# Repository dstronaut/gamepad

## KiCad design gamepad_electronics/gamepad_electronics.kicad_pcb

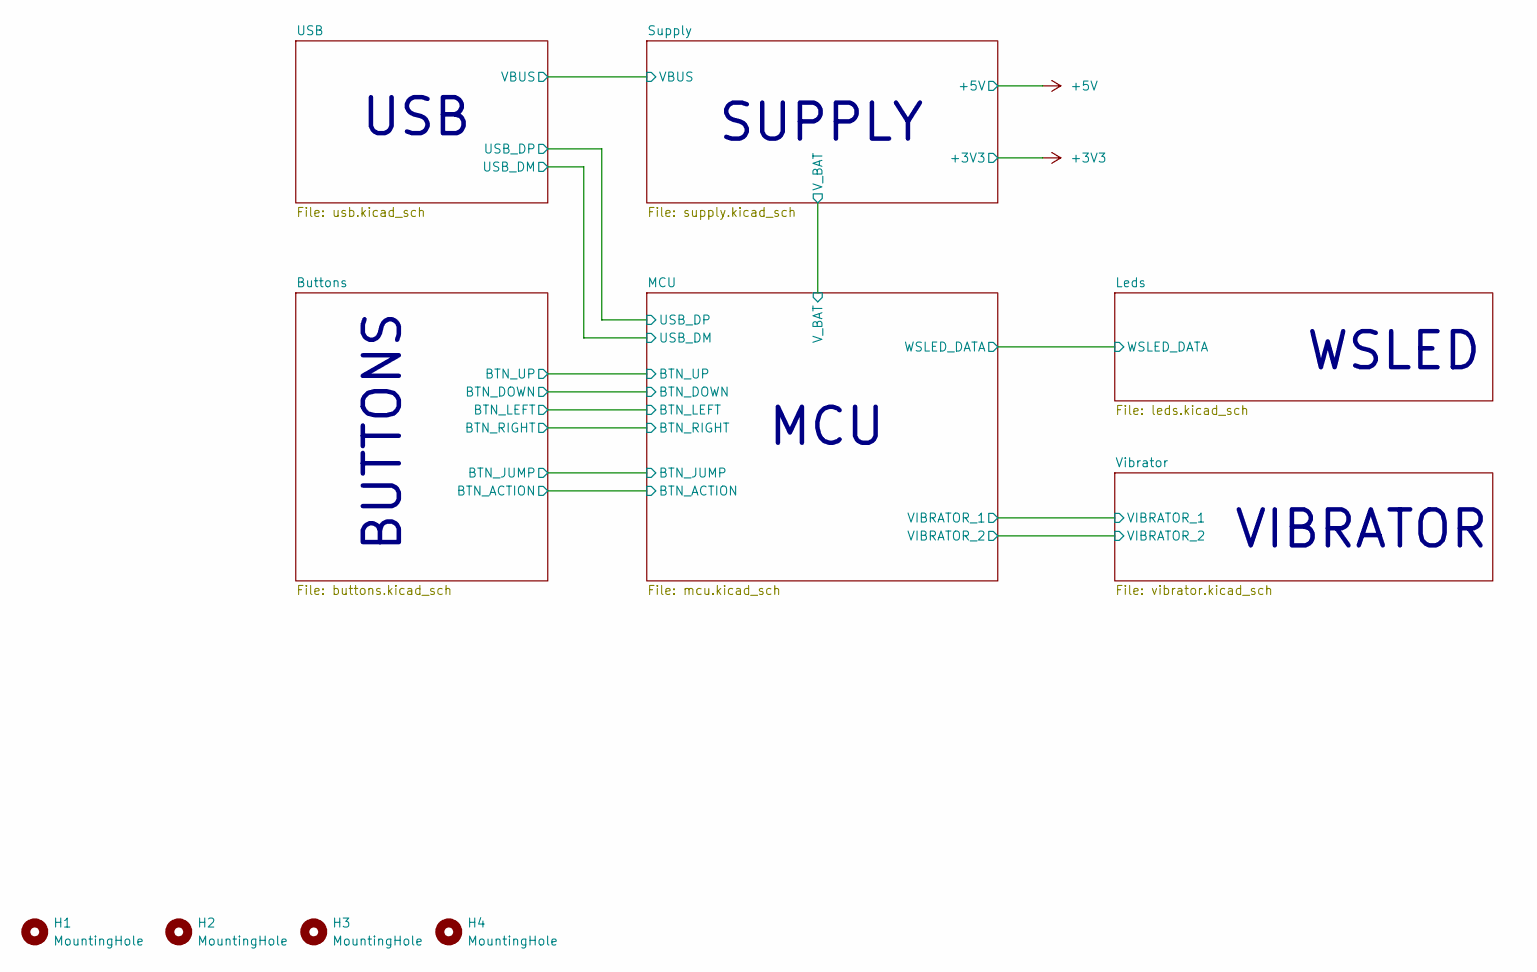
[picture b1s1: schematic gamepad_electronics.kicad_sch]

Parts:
H1, H2, H3, H4: MountingHole; MountingHole_3.2mm_M3_ISO14580

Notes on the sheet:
USB
SUPPLY
BUTTONS
WSLED
MCU
VIBRATOR

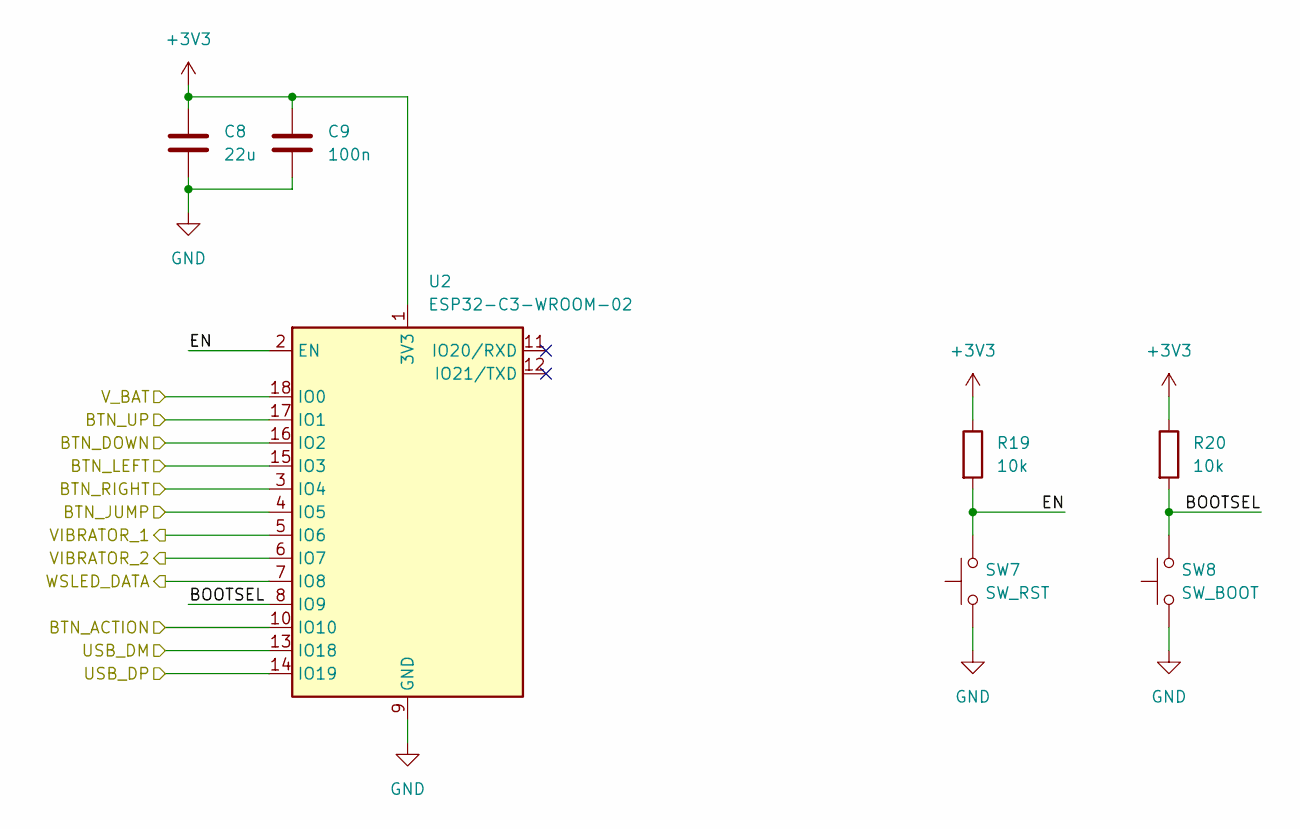
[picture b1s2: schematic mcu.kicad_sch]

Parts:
C8: 22u; C_0805_2012Metric
C9: 100n; C_0603_1608Metric
R19, R20: 10k; R_0603_1608Metric
SW7: SW_RST; SW_SPST_TL3342
SW8: SW_BOOT; SW_SPST_TL3342
U2: ESP32-C3-WROOM-02

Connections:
+3V3: C8.1, C9.1, R19.1, R20.1, U2.1 (3V3); also elsewhere on the board
/Buttons/BTN_ACTION: U2.10 (IO10); also elsewhere on the board
/Buttons/BTN_DOWN: U2.16 (IO2); also elsewhere on the board
/Buttons/BTN_JUMP: U2.4 (IO5); also elsewhere on the board
/Buttons/BTN_LEFT: U2.15 (IO3); also elsewhere on the board
/Buttons/BTN_RIGHT: U2.3 (IO4); also elsewhere on the board
/Buttons/BTN_UP: U2.17 (IO1); also elsewhere on the board
/Leds/WSLED_DATA: U2.7 (IO8); also elsewhere on the board
/MCU/BOOTSEL: R20.2, SW8.2, U2.8 (IO9)
/MCU/EN: R19.2, SW7.2, U2.2 (EN)
/MCU/USB_DM: U2.13 (IO18); also elsewhere on the board
/MCU/USB_DP: U2.14 (IO19); also elsewhere on the board
/MCU/VIBRATOR_1: U2.5 (IO6); also elsewhere on the board
/MCU/VIBRATOR_2: U2.6 (IO7); also elsewhere on the board
/MCU/V_BAT: U2.18 (IO0); also elsewhere on the board
GND: C8.2, C9.2, SW7.1, SW8.1, U2.9 (GND), U2.19 (GND); also elsewhere on the board

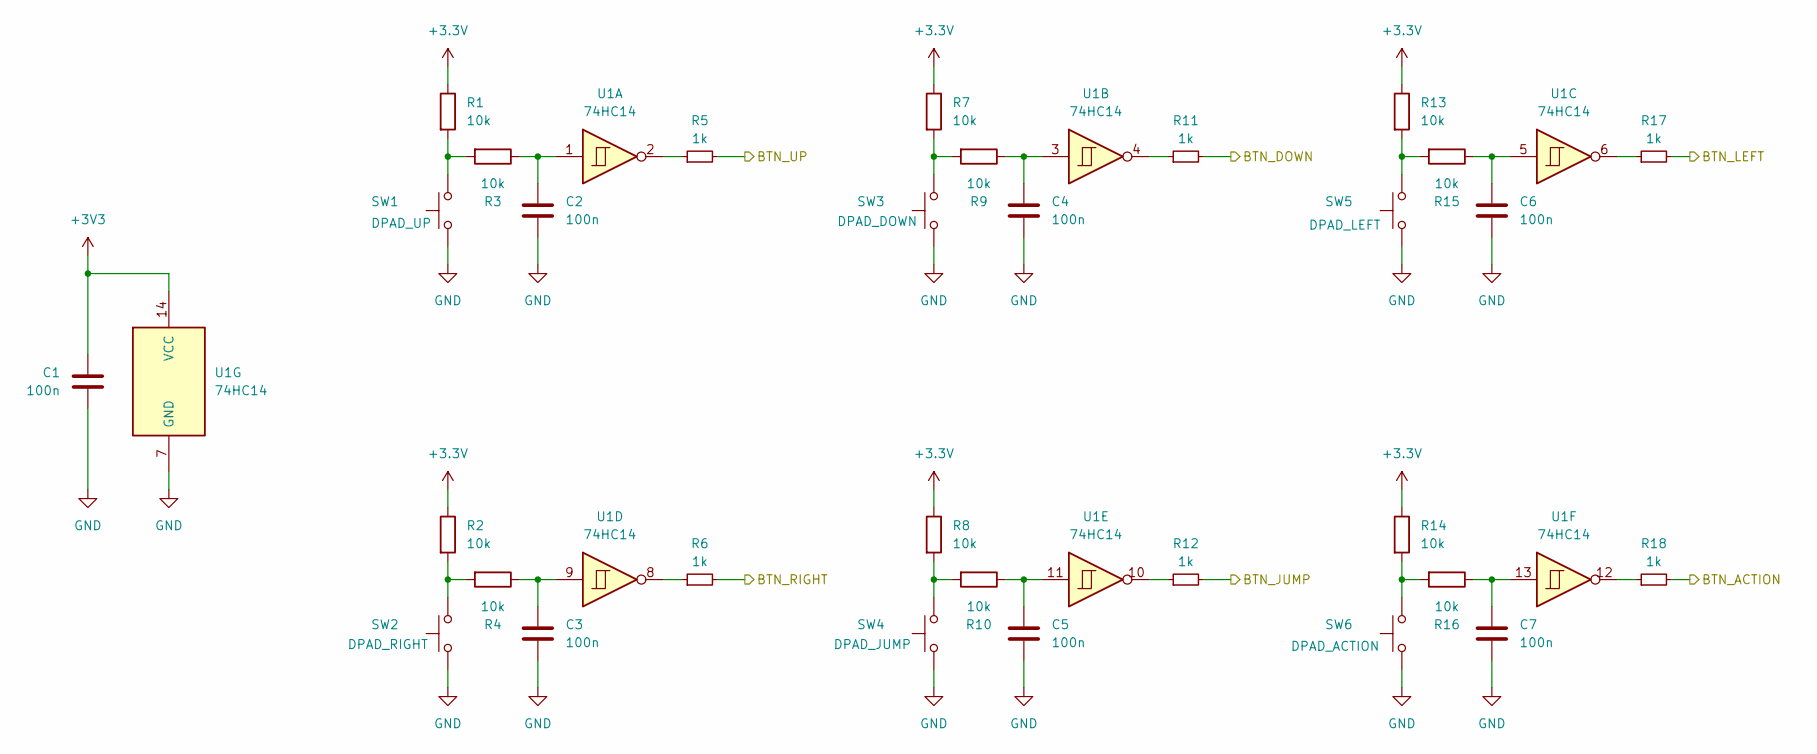
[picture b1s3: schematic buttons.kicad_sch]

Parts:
C1, C2, C3, C4, C5, C6, C7: 100n; C_0603_1608Metric
R1, R2, R3, R4, R7, R8, R9, R10, R13, R14, R15, R16: 10k; R_0603_1608Metric
R5, R6, R11, R12, R17, R18: 1k; R_0603_1608Metric
SW1: DPAD_UP; SW_PUSH_6mm_H7.3mm
SW2: DPAD_RIGHT; SW_PUSH_6mm_H7.3mm
SW3: DPAD_DOWN; SW_PUSH_6mm_H7.3mm
SW4: DPAD_JUMP; SW_PUSH_6mm_H7.3mm
SW5: DPAD_LEFT; SW_PUSH_6mm_H7.3mm
SW6: DPAD_ACTION; SW_PUSH_6mm_H7.3mm
U1: 74HC14; SOIC-14_3.9x8.7mm_P1.27mm

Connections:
+3.3V: R1.1, R2.1, R7.1, R8.1, R13.1, R14.1
+3V3: C1.2, U1.14 (VCC); also elsewhere on the board
/Buttons/BTN_ACTION: R18.2; also elsewhere on the board
/Buttons/BTN_DOWN: R11.2; also elsewhere on the board
/Buttons/BTN_JUMP: R12.2; also elsewhere on the board
/Buttons/BTN_LEFT: R17.2; also elsewhere on the board
/Buttons/BTN_RIGHT: R6.2; also elsewhere on the board
/Buttons/BTN_UP: R5.2; also elsewhere on the board
GND: C1.1, C2.2, C3.2, C4.2, C5.2, C6.2, C7.2, SW1.1, SW2.1, SW3.1, SW4.1, SW5.1, SW6.1, U1.7 (GND); also elsewhere on the board
unnamed: C2.1, R3.1, U1.1
unnamed: C3.1, R4.1, U1.9
unnamed: C4.1, R9.1, U1.3
unnamed: C5.1, R10.1, U1.11
unnamed: C6.1, R15.1, U1.5
unnamed: C7.1, R16.1, U1.13
unnamed: R1.2, R3.2, SW1.2
unnamed: R2.2, R4.2, SW2.2
unnamed: R5.1, U1.2
unnamed: R6.1, U1.8
unnamed: R7.2, R9.2, SW3.2
unnamed: R8.2, R10.2, SW4.2
unnamed: R11.1, U1.4
unnamed: R12.1, U1.10
unnamed: R13.2, R15.2, SW5.2
unnamed: R14.2, R16.2, SW6.2
unnamed: R17.1, U1.6
unnamed: R18.1, U1.12

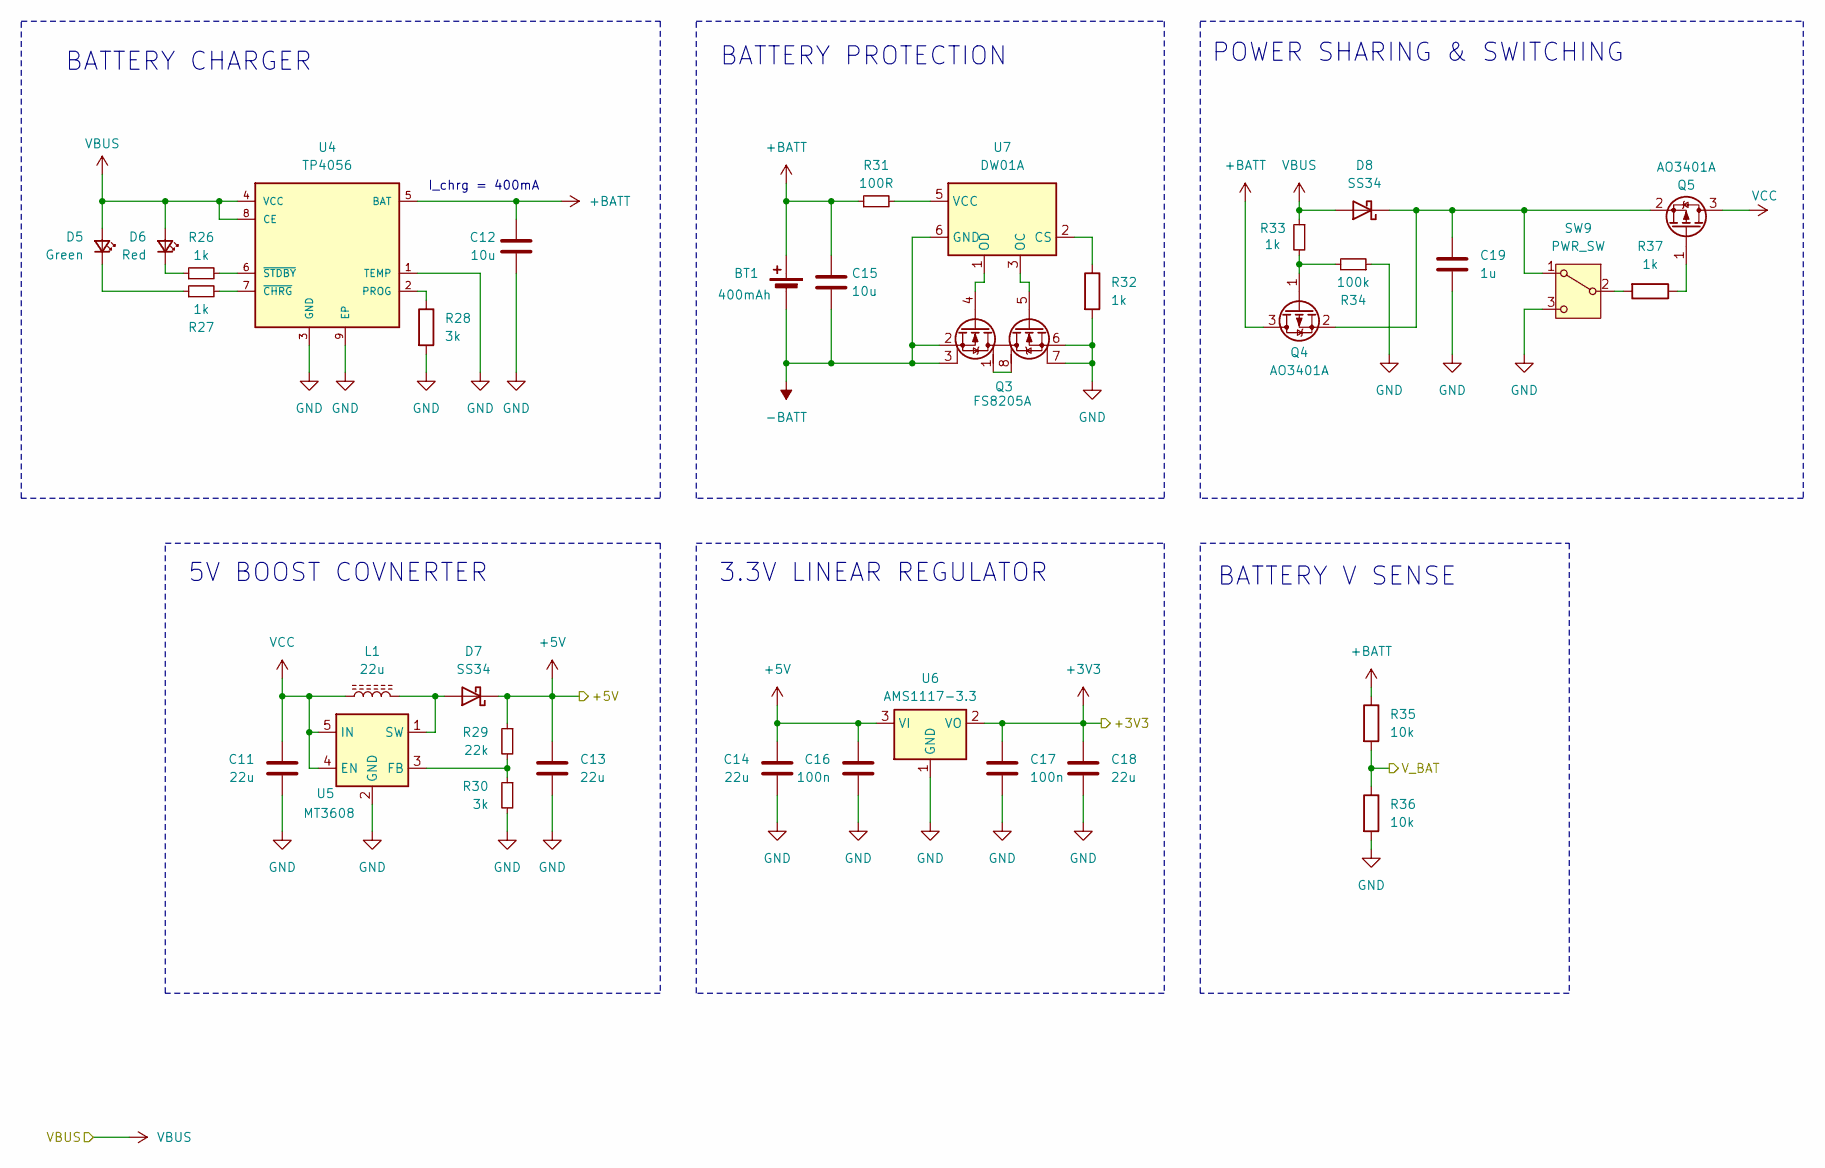
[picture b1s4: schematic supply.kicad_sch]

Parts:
BT1: 400mAh; JST_PH_S2B-PH-K_1x02_P2.00mm_Horizontal
C11, C13, C14, C18: 22u; C_0805_2012Metric
C12, C15: 10u; C_0805_2012Metric
C16, C17: 100n; C_0603_1608Metric
C19: 1u; C_0805_2012Metric
D5: Green; LED_0805_2012Metric
D6: Red; LED_0805_2012Metric
D7, D8: SS34; D_SMA
L1: 22u; L_SXN_SMDRI127
Q3: FS8205A; TSSOP-8_4.4x3mm_P0.65mm
Q4, Q5: AO3401A; SOT-23
R26, R27, R32, R33, R37: 1k; R_0603_1608Metric
R28, R30: 3k; R_0603_1608Metric
R29: 22k; R_0603_1608Metric
R31: 100R; R_0603_1608Metric
R34: 100k; R_0603_1608Metric
R35, R36: 10k; R_0603_1608Metric
SW9: PWR_SW; SW_SPDT_PCM12
U4: TP4056; HTSOP-8-1EP_3.9x4.9mm_P1.27mm_EP2.4x3.2mm_ThermalVias
U5: MT3608; SOT-23-6
U6: AMS1117-3.3; SOT-223-3_TabPin2
U7: DW01A; SOT-23-6

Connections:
+3V3: C17.1, C18.1, U6.2 (VO); also elsewhere on the board
+5V: C13.1, C14.1, C16.2, D7.1 (K), R29.1, U6.3 (VI); also elsewhere on the board
+BATT: BT1.1 (+), C12.1, C15.1, Q4.3 (D), R31.1, R35.1, U4.5 (BAT)
-BATT: BT1.2 (-), C15.2, Q3.2 (S1), Q3.3 (S1), U7.6 (GND)
/MCU/V_BAT: R35.2, R36.1; also elsewhere on the board
GND: C11.2, C12.2, C13.2, C14.2, C16.1, C17.2, C18.2, C19.2, Q3.6 (S2), Q3.7 (S2), R28.2, R30.2, R32.2, R34.1, R36.2, SW9.3 (C), U4.1 (TEMP), U4.3 (GND), U4.9 (EP), U5.2 (GND), U6.1 (GND); also elsewhere on the board
unnamed: D5.1 (K), R27.1
unnamed: D6.1 (K), R26.1
unnamed: D7.2 (A), L1.2, U5.1 (SW)
unnamed: C19.1, D8.1 (K), Q4.2 (S), Q5.2 (S), SW9.1 (A)
unnamed: Q3.1 (D12), Q3.8 (D12)
unnamed: Q3.4 (G1), U7.1 (OD)
unnamed: Q3.5 (G), U7.3 (OC)
unnamed: Q4.1 (G), R33.2, R34.2
unnamed: Q5.1 (G), R37.1
unnamed: R37.2, SW9.2 (B)
unnamed: R28.1, U4.2 (PROG)
unnamed: R27.2, U4.7 (~CHRG)
unnamed: R26.2, U4.6 (~STDBY)
unnamed: R29.2, R30.1, U5.3 (FB)
unnamed: R32.1, U7.2 (CS)
unnamed: R31.2, U7.5 (VCC)
VBUS: D5.2 (A), D6.2 (A), D8.2 (A), R33.1, U4.4 (VCC), U4.8 (CE); also elsewhere on the board
VCC: C11.1, L1.1, Q5.3 (D), U5.4 (EN), U5.5 (IN)

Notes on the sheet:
BATTERY PROTECTION
BATTERY V SENSE
3.3V LINEAR REGULATOR
POWER SHARING & SWITCHING
BATTERY CHARGER
I_chrg = 400mA
5V BOOST COVNERTER

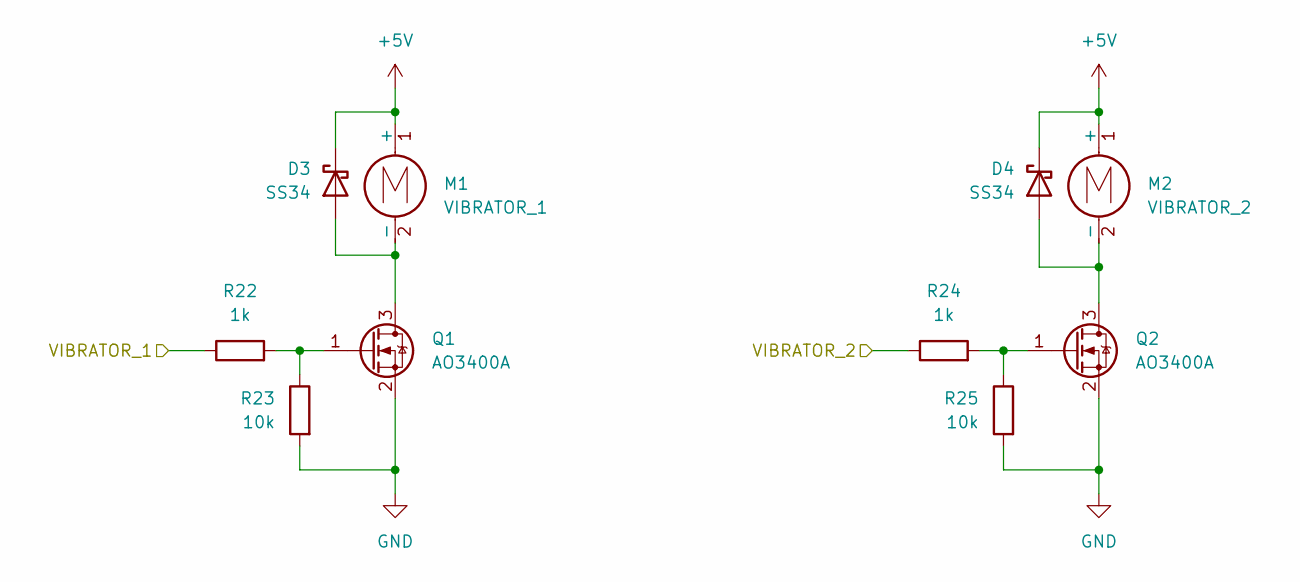
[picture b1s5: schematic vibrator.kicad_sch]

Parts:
D3, D4: SS34; D_SMA
M1: VIBRATOR_1; JST_PH_S2B-PH-K_1x02_P2.00mm_Horizontal
M2: VIBRATOR_2; JST_PH_S2B-PH-K_1x02_P2.00mm_Horizontal
Q1, Q2: AO3400A; SOT-23
R22, R24: 1k; R_0603_1608Metric
R23, R25: 10k; R_0603_1608Metric

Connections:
+5V: D3.1 (K), D4.1 (K), M1.1 (+), M2.1 (+); also elsewhere on the board
/MCU/VIBRATOR_1: R22.1; also elsewhere on the board
/MCU/VIBRATOR_2: R24.1; also elsewhere on the board
GND: Q1.2 (S), Q2.2 (S), R23.2, R25.2; also elsewhere on the board
unnamed: D3.2 (A), M1.2 (-), Q1.3 (D)
unnamed: D4.2 (A), M2.2 (-), Q2.3 (D)
unnamed: Q1.1 (G), R22.2, R23.1
unnamed: Q2.1 (G), R24.2, R25.1

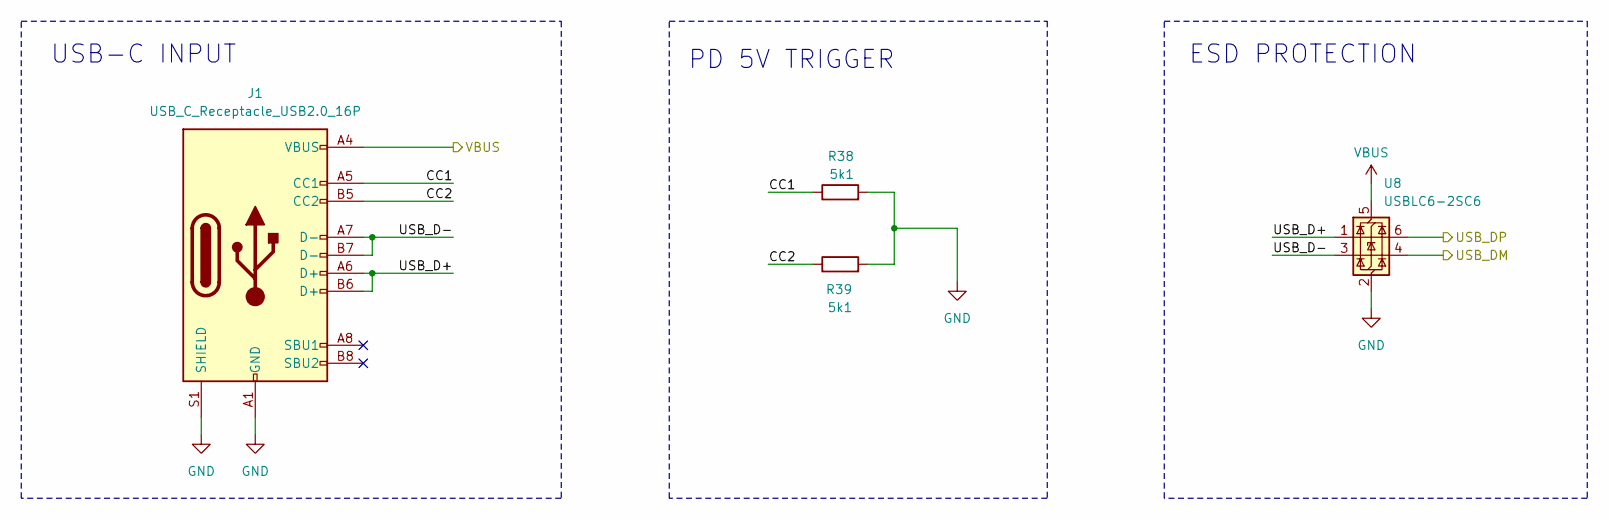
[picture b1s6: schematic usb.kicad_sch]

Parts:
J1: USB_C_Receptacle_USB2.0_16P; USB_C_Receptacle_GCT_USB4105-xx-A_16P_TopMnt_Horizontal
R38, R39: 5k1; R_0603_1608Metric
U8: USBLC6-2SC6; SOT-23-6

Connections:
/MCU/USB_DM: U8.4 (I/O2); also elsewhere on the board
/MCU/USB_DP: U8.6 (I/O1); also elsewhere on the board
/USB/CC1: J1.A5 (CC1), R38.1
/USB/CC2: J1.B5 (CC2), R39.1
/USB/USB_D+: J1.A6 (D+), J1.B6 (D+), U8.1 (I/O1)
/USB/USB_D-: J1.A7 (D-), J1.B7 (D-), U8.3 (I/O2)
GND: J1.A1 (GND), J1.A12 (GND), J1.B1 (GND), J1.B12 (GND), J1.S1 (SHIELD), R38.2, R39.2, U8.2 (GND); also elsewhere on the board
VBUS: J1.A4 (VBUS), J1.A9 (VBUS), J1.B4 (VBUS), J1.B9 (VBUS), U8.5 (VBUS); also elsewhere on the board

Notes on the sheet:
ESD PROTECTION
PD 5V TRIGGER
USB-C INPUT

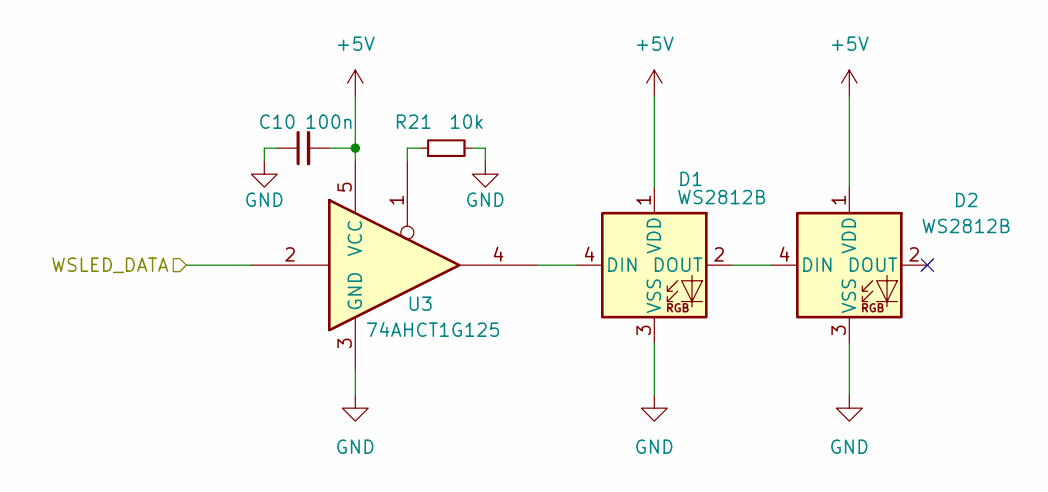
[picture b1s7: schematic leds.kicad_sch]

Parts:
C10: 100n; C_0603_1608Metric
D1, D2: WS2812B; LED_WS2812B-Mini_PLCC4_3.5x3.5mm
R21: 10k; R_0603_1608Metric
U3: 74AHCT1G125; SOT-23-5

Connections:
+5V: C10.2, D1.1 (VDD), D2.1 (VDD), U3.5 (VCC); also elsewhere on the board
/Leds/WSLED_DATA: U3.2; also elsewhere on the board
GND: C10.1, D1.3 (VSS), D2.3 (VSS), R21.2, U3.3 (GND); also elsewhere on the board
unnamed: D1.4 (DIN), U3.4
unnamed: D1.2 (DOUT), D2.4 (DIN)
unnamed: R21.1, U3.1

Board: 2 copper layers, 97 parts (4 on the bottom side), 67 nets, no tracks yet.

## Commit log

2024-11-19 init
